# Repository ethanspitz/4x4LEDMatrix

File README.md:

4x4LEDMatrix
============

4x4 LED Matrix uses ATTINY85 with three 74-595s each with their own serial in from the ATTINY85. One used for ground connections on the matrix, two used for anode connections for controlling color. BS270 N-Channel Mosfets used for draining current on each row.

###Plans on adding:
* Power Connection
* Voltage Regulator
* Connection for daisy chaining multiple boards???
* Switch for disabling light output
* Code

###Bugs to be fixed:
* Overlaping pads on every LED
* VCC/GND on 74595s

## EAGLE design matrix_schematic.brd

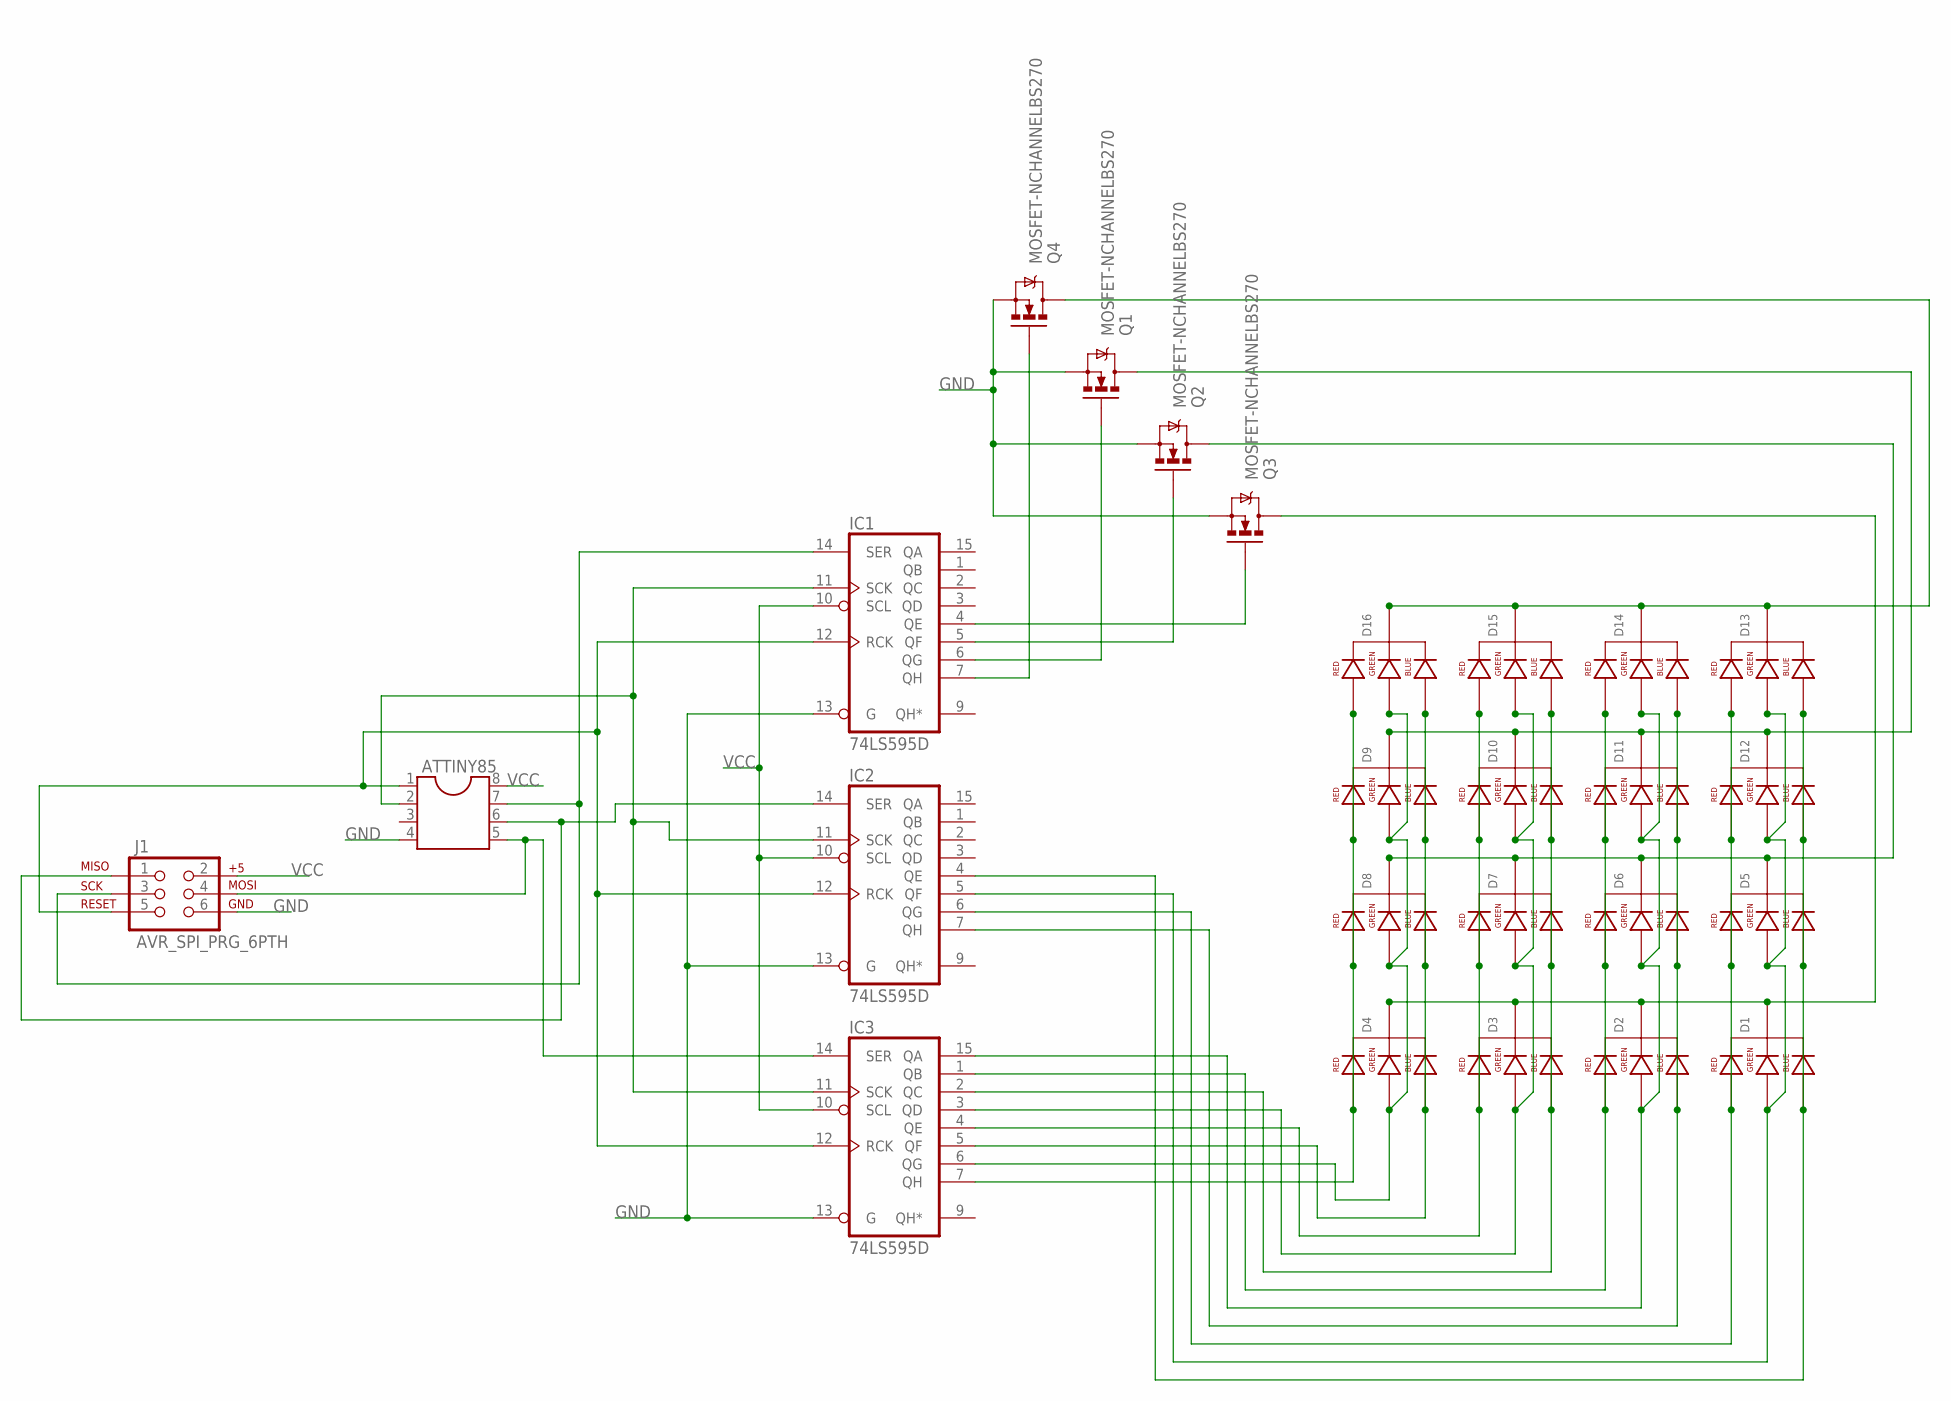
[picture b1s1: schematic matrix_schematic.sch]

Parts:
ATTINY85: DIL8; DIL08
D1, D2, D3, D4, D5, D6, D7, D8, D9, D10, D11, D12, D13, D14, D15, D16: LED-RGB-CC-THRUDIFFUSE; LED-RGB-THRU
IC1, IC2, IC3: 74LS595D; SO16
J1: AVR_SPI_PRG_6PTH; 2X3
Q1, Q2, Q3, Q4: MOSFET-NCHANNELBS270; TO-92

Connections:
GND: ATTINY85.4, IC1.8 (GND), IC1.13 (G), IC2.8 (GND), IC2.13 (G), IC3.8 (GND), IC3.13 (G), J1.6, Q1.3 (S), Q2.3 (S), Q3.3 (S), Q4.3 (S)
unnamed: ATTINY85.1, IC1.12 (RCK), IC2.12 (RCK), IC3.12 (RCK), J1.5
unnamed: ATTINY85.2, IC1.11 (SCK), IC2.11 (SCK), IC3.11 (SCK)
unnamed: D1.3 (GREEN_CATHODE), D5.3 (GREEN_CATHODE), D12.3 (GREEN_CATHODE), D13.3 (GREEN_CATHODE), IC2.5 (QF)
unnamed: D1.4 (BLUE_CATHODE), D5.4 (BLUE_CATHODE), D12.4 (BLUE_CATHODE), D13.4 (BLUE_CATHODE), IC2.4 (QE)
unnamed: D1.1 (RED_CATHODE), D5.1 (RED_CATHODE), D12.1 (RED_CATHODE), D13.1 (RED_CATHODE), IC2.6 (QG)
unnamed: D2.4 (BLUE_CATHODE), D6.4 (BLUE_CATHODE), D11.4 (BLUE_CATHODE), D14.4 (BLUE_CATHODE), IC2.7 (QH)
unnamed: D2.3 (GREEN_CATHODE), D6.3 (GREEN_CATHODE), D11.3 (GREEN_CATHODE), D14.3 (GREEN_CATHODE), IC3.15 (QA)
unnamed: D2.1 (RED_CATHODE), D6.1 (RED_CATHODE), D11.1 (RED_CATHODE), D14.1 (RED_CATHODE), IC3.1 (QB)
unnamed: D3.4 (BLUE_CATHODE), D7.4 (BLUE_CATHODE), D10.4 (BLUE_CATHODE), D15.4 (BLUE_CATHODE), IC3.2 (QC)
unnamed: D4.4 (BLUE_CATHODE), D8.4 (BLUE_CATHODE), D9.4 (BLUE_CATHODE), D16.4 (BLUE_CATHODE), IC3.5 (QF)
unnamed: D4.3 (GREEN_CATHODE), D8.3 (GREEN_CATHODE), D9.3 (GREEN_CATHODE), D16.3 (GREEN_CATHODE), IC3.6 (QG)
unnamed: D4.1 (RED_CATHODE), D8.1 (RED_CATHODE), D9.1 (RED_CATHODE), D16.1 (RED_CATHODE), IC3.7 (QH)
unnamed: D13.2 (CATHODE), D14.2 (CATHODE), D15.2 (CATHODE), D16.2 (CATHODE), Q4.1 (D)
unnamed: D1.2 (CATHODE), D2.2 (CATHODE), D3.2 (CATHODE), D4.2 (CATHODE), Q3.1 (D)
unnamed: D5.2 (CATHODE), D6.2 (CATHODE), D7.2 (CATHODE), D8.2 (CATHODE), Q2.1 (D)
unnamed: D9.2 (CATHODE), D10.2 (CATHODE), D11.2 (CATHODE), D12.2 (CATHODE), Q1.1 (D)
unnamed: ATTINY85.7, IC1.14 (SER), J1.3
unnamed: ATTINY85.6, IC2.14 (SER), J1.1
unnamed: ATTINY85.5, IC3.14 (SER), J1.4
unnamed: D3.3 (GREEN_CATHODE), D7.3 (GREEN_CATHODE), D10.3 (GREEN_CATHODE), D15.3 (GREEN_CATHODE), IC3.3 (QD)
unnamed: D3.1 (RED_CATHODE), D7.1 (RED_CATHODE), D10.1 (RED_CATHODE), D15.1 (RED_CATHODE), IC3.4 (QE)
unnamed: IC1.7 (QH), Q4.2 (G)
unnamed: IC1.6 (QG), Q1.2 (G)
unnamed: IC1.5 (QF), Q2.2 (G)
unnamed: IC1.4 (QE), Q3.2 (G)
VCC: ATTINY85.8, IC1.10 (SCL), IC1.16 (VCC), IC2.10 (SCL), IC2.16 (VCC), IC3.10 (SCL), IC3.16 (VCC), J1.2

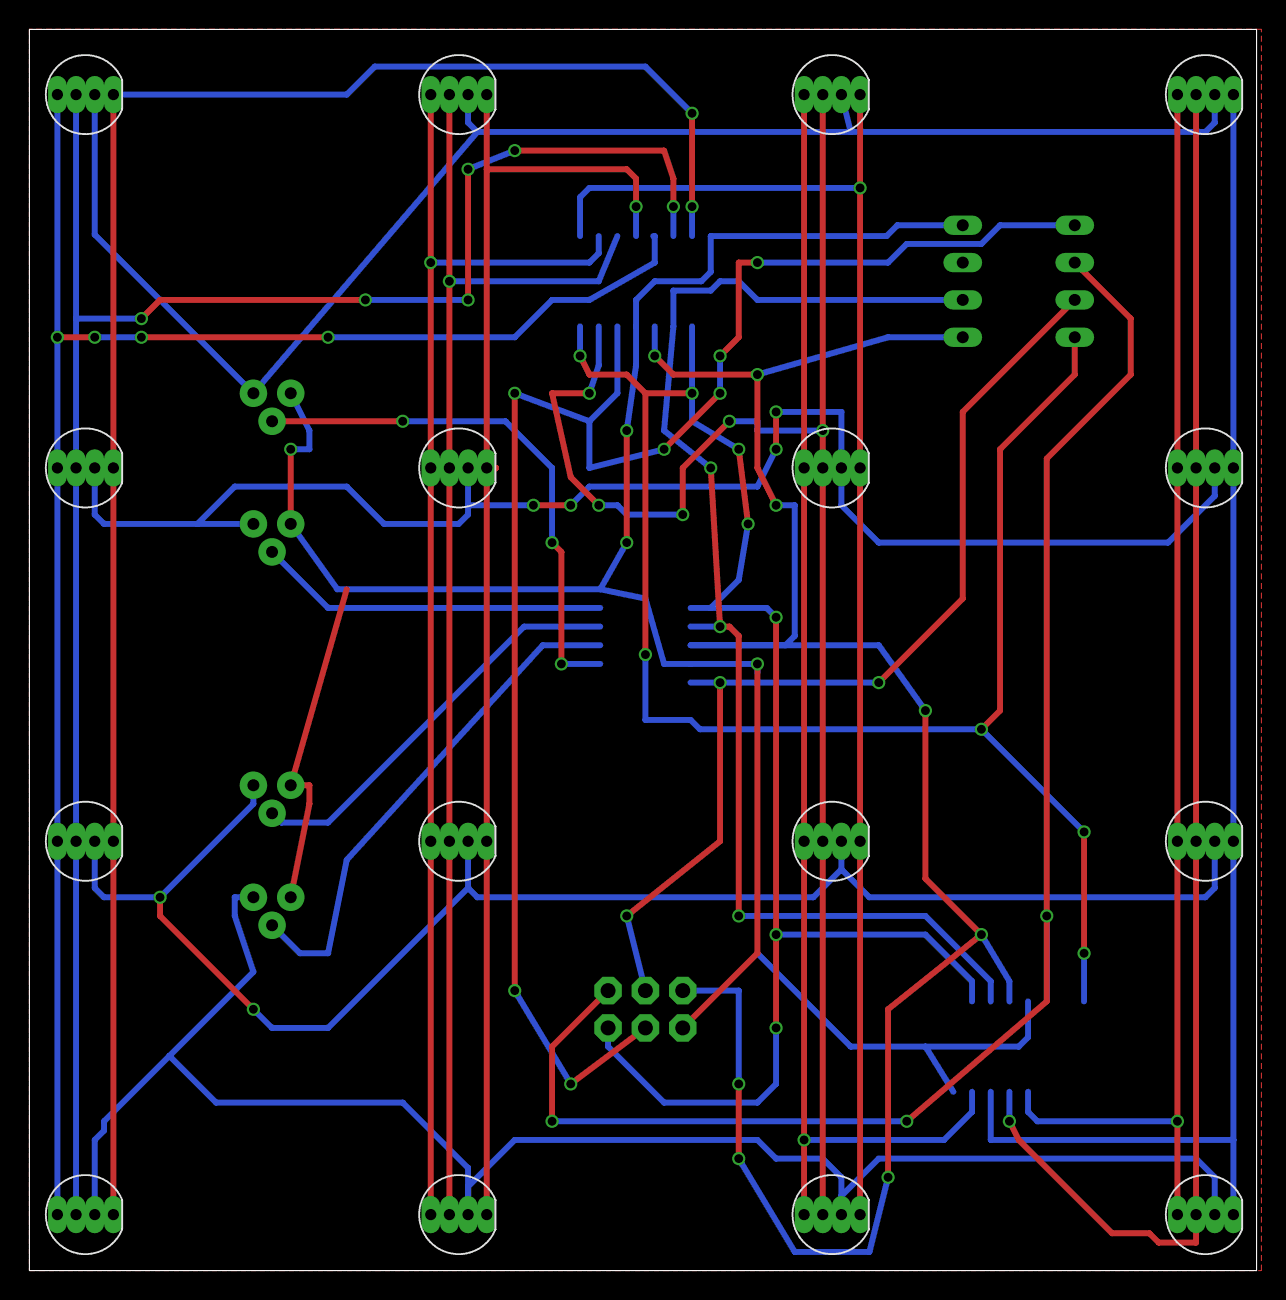
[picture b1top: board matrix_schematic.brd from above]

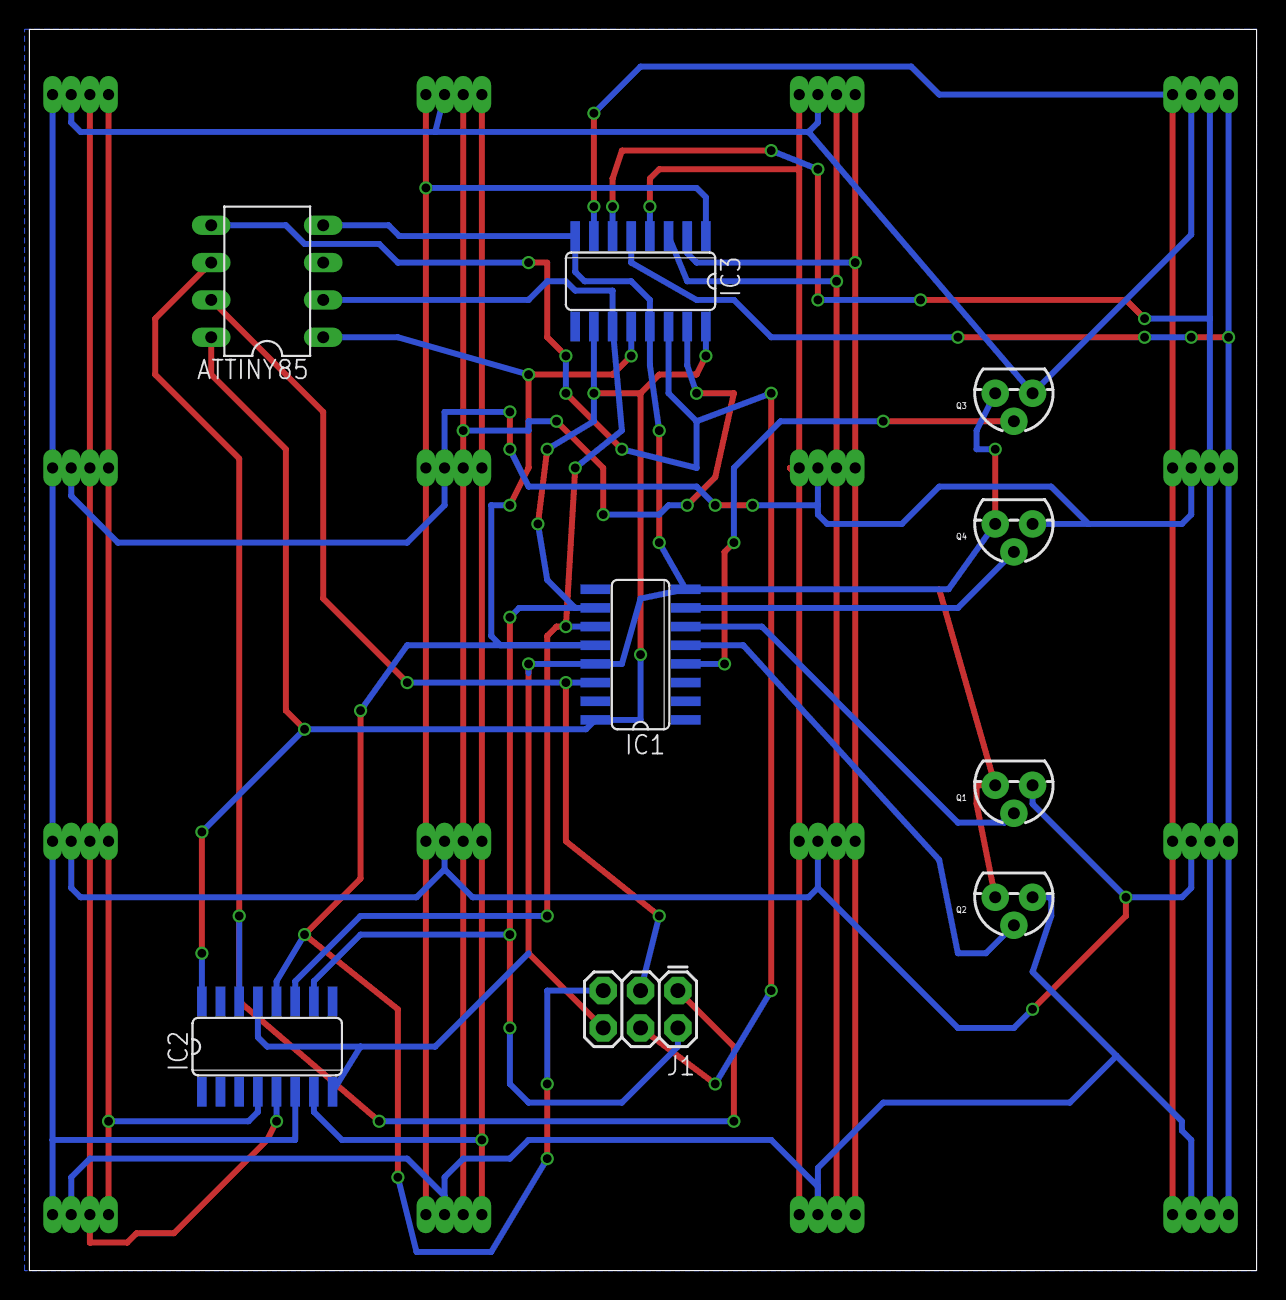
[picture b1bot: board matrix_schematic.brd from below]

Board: 2 copper layers, 83.5 x 84.4 mm, 25 parts (9 on the bottom side), 27 nets.

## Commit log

2013-03-03 Initial Commit
    Initial work on the schematic
2013-03-04 Finished initial schematic
    Uses ATTINY85 with three 74-595s each with their own serial in from the
    ATTINY85. One used for ground connections on the matrix, two used for
    anode connections for controlling color. BS270 N-Channel Mosfets used
    for draining current on each row.
2013-03-04 Updated .gitignore to remove backup schematic files from git
2013-03-04 Initial commit of board layout and fixes to schematic
    One airwire left on board and optimization needed as there are a bunch
    of uneccesary traces.
2013-03-04 Fixed airwire
2013-03-04 Fixed a bunch of overlaps
    Still many overlaps, the RGB LED footprint I used overlaps every pad.
2013-03-04 Updated to ignore the eagle.epf file
    file is only used for storing in program, project specific settings
2013-03-04 Revert "Updated to ignore the eagle.epf file"
    This reverts commit f92bfbe0c4869d34c19d1d61f4fc79a4752a2629.
2013-03-06 Added ISP header for programming
2013-03-06 Update design rules to use ITEADstudio DRC file
2013-03-12 Fixed MD on Readme
2013-03-12 Update formatting

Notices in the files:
parts and their libraries:
SparkFun-LED: Licensing: CC v3.0 Share-Alike You are welcome to use this library for commercial purposes.
